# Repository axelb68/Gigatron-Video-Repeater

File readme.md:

# Gigatron Video Repeater

The video repeater is a small add-on board for the Gigatron TTL computer (https://gigatron.io) to offload the task of duplicating video lines. Every first line out of four is written to an on-board memory and autonomously transmitted 4 times to the VGA output. By this the Gigatron can always be run in mode 3 and is still producing a screen output without blanked lines.

Main component is the asynchronous FIFO memory chip SN74ACT7201 (or compatible, see below) which is constructed with dual-port SRAM and internal write and read address counters. The read pointer can be reset independently of the write pointer for retransmitting previously read data.

The first video line (out of four) writes each pixel to the memory which is followed by an immediate read. This is like a flow-through operation
which simply copies the pixel information back to the output.
A retransmit of the complete line is then performed for the next three HSYNC cycles.

The schematics of the repeater shows connector U1A which can be plugged into the U37 output register socket of the Gigatron. HSYNC is divided by two JK flipflops (U2). The result is used to initialize the internal read and write pointers of the SN74ACT7201 to the first location. A 74HCT574 latches the memory output and passes it back to connector U1A for VGA output.
By means of a "scanlines on/off" jumper (JP1) the primary line can be blanked-out in order to create a "scanline look" similar to mode 1 of the Gigatron.

So far I tested the board with different clones/extensions of the SN74ACT7201. IDT7201-15, IDT7202-25, and QS7204-15 worked fine.
The picture shows a mixture of 74F, 74ACT, and 74LS components which is not important, however. It is sufficient to use the HCT versions or even LS for the flipflops and the logic.

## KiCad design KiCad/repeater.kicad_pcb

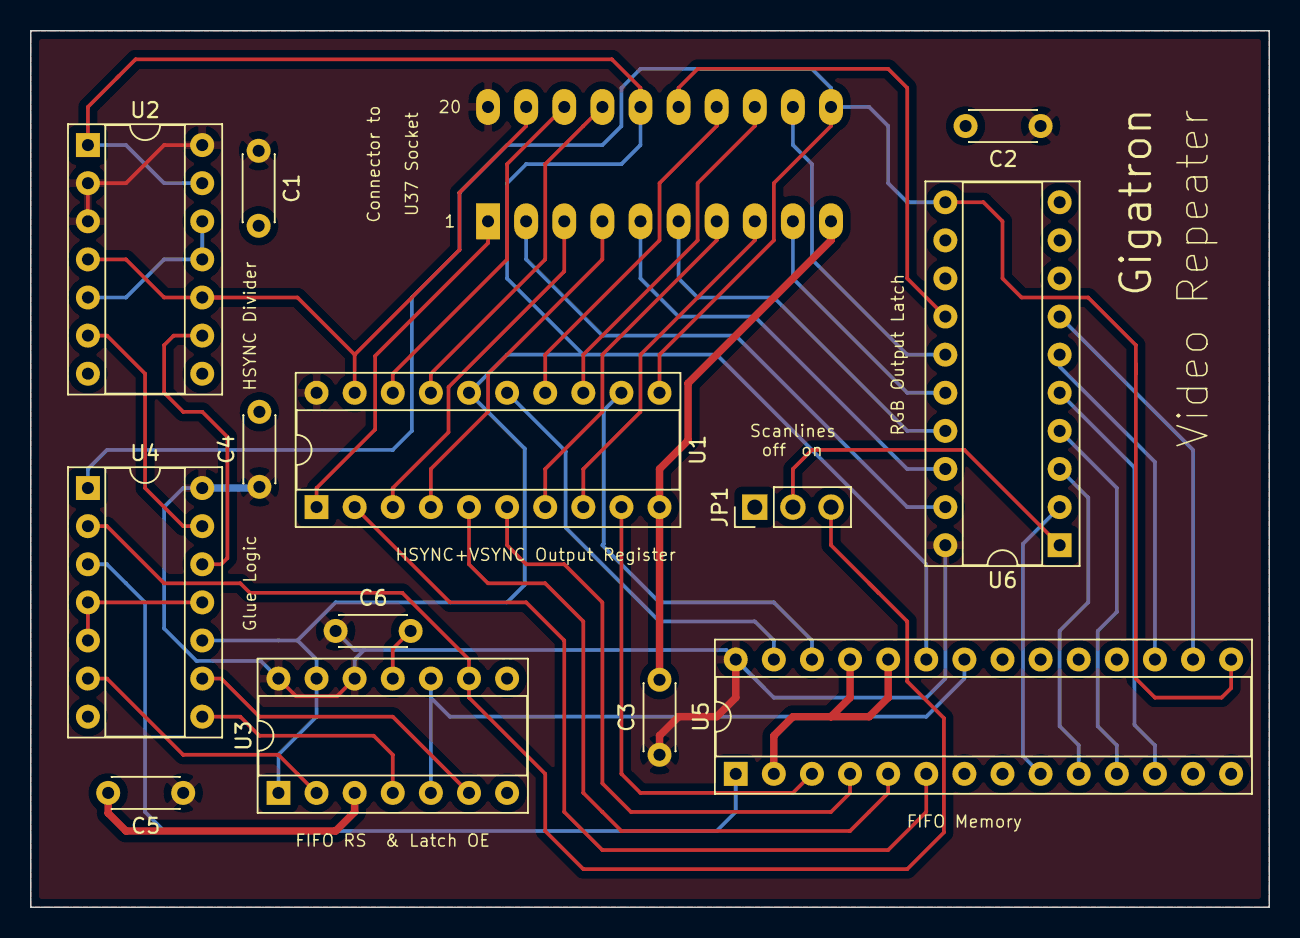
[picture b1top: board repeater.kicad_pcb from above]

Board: 2 copper layers, 82.6 x 58.4 mm, 14 parts (0 on the bottom side), 43 nets.

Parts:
C1, C2, C3, C4, C5, C6: 100nF; C_Disc_D4.3mm_W1.9mm_P5.00mm
JP1: Jumper_NC_Dual; PinHeader_1x03_P2.54mm_Vertical
U1: 74HCT377; DIP-20_W7.62mm_Socket
U1A1: Connector; DIP-20_W7.62mm_Socket_LongPads
U2, U3: 74LS113; DIP-14_W7.62mm_Socket
U4: 74LS00; DIP-14_W7.62mm_Socket
U5: SN74ACT7201; DIP-28_W7.62mm_Socket
U6: 74HCT574; DIP-20_W7.62mm_Socket

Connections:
/BH: U1.15, U5.27
/BL: U1.12, U5.26
/D0: U1.3, U1A1.3
/D1: U1.4, U1A1.4
/D2: U1.7, U1A1.7
/D3: U1.8, U1A1.8
/D4: U1.13, U1A1.13
/D5: U1.14, U1A1.14
/D6: U1.17, U1A1.17
/D7: U1.18, U1A1.18
/F0: U5.9, U6.2
/F1: U5.10, U6.3
/F2: U5.11, U6.4
/F3: U5.12, U6.5
/F4: U5.16, U6.7
/F5: U5.17, U6.6
/GH: U1.9, U5.3
/GL: U1.6, U5.4
/Q0: U1A1.2, U6.19
/Q1: U1A1.5, U6.18
/Q2: U1A1.6, U6.17
/Q3: U1A1.9, U6.16
/Q4: U1A1.12, U6.15
/Q5: U1A1.15, U6.14
/RH: U1.5, U5.5
/RL: U1.2, U5.6
GND: C1.2, C2.2, C3.2, C4.2, C5.2, C6.2, JP1.1, U1.10, U1A1.10, U2.7, U3.3, U3.7, U3.11, U4.7, U5.2, U5.7, U5.14, U5.24, U5.25, U6.8, U6.9, U6.10
unnamed: JP1.2, U6.1
unnamed: JP1.3, U3.9, U4.2
unnamed: U1.1, U1A1.1
unnamed: U1.11, U1A1.11, U4.1, U5.15, U6.11
unnamed: U1.16, U1A1.16, U2.1, U2.13, U3.1, U3.13, U4.10, U5.23
unnamed: U1.19, U1A1.19, U2.4, U2.10
unnamed: U2.6, U4.13
unnamed: U2.9, U4.12
unnamed: U2.5, U2.11, U2.12
unnamed: U3.2, U4.6
unnamed: U3.4, U4.8
unnamed: U3.6, U4.9
unnamed: U3.5, U3.10, U5.22
unnamed: U4.3, U5.1
unnamed: U4.4, U4.5, U4.11
VCC: C1.1, C2.1, C3.1, C4.1, C5.1, C6.1, U1.20, U1A1.20, U2.2, U2.3, U2.14, U3.12, U3.14, U4.14, U5.28, U6.20

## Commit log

2021-06-01 Create coming soon
2023-05-10 untested
